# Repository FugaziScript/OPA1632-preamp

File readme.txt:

#OPA1632 preamp

przedwzmacniacz z 2 kanałami, sterowanymi przez przekaźniki. Na wyjściu jest sygnał symetryczny (potrzebny do wysterowania TPA3255). 
Na wejściu akceptowane są sygnały symetryczne, jaki i niesymetryczne. OPA1632 jest w stanie  symetryzować sygnał single-ended, jeżeli jedno z wejść jest dołączone do masy. Zasilanie układów jest z pojedyńczego +12V. Poprzez przetwornicę generującą napięcie ujemne oraz stabilizatory gwarantujące niskie szumy, nie ma potrzeby stosować kondensatorów na wyjściu OPA1632. Wzmocnienie układu wynosi 1. 
Płytka pcb jest bardzo ciasno upakowana, gdyż w obudowie nie było dużo miejsca (jest to największe pcb jakie się zmieściło). Wykonane w technologii tht ze względów na koszty oraz brak precyzji przy wytrawianiu płytki oraz lutowaniu elementów smd.

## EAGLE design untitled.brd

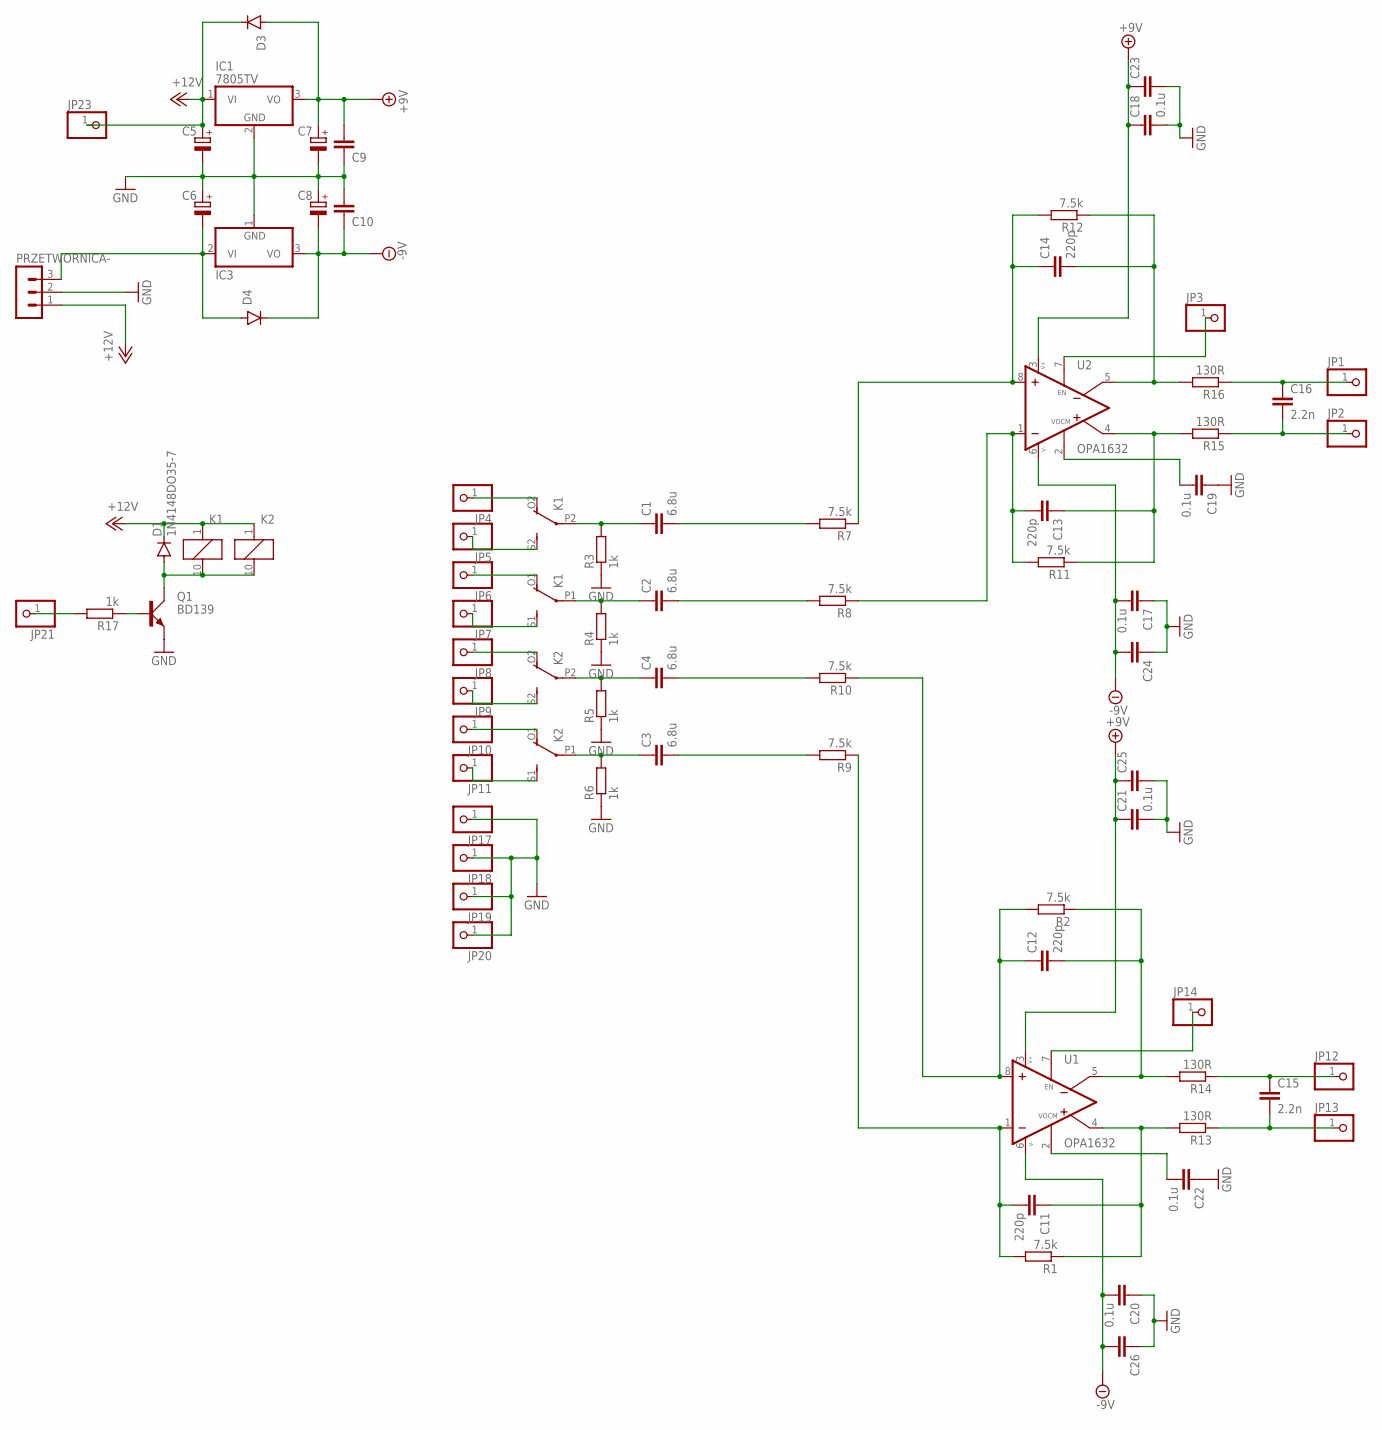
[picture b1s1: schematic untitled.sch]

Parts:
C1, C2, C3, C4: 6.8u; C5B7.2
C5, C6, C7, C8: CPOL-EUE3.5-8; E3,5-8
C9, C10, C23, C24, C25, C26: C-EU050-024X044; C050-024X044
C11, C12, C13, C14: 220p; C075-032X103
C15, C16: 2.2n; C025-024X044
C17, C18, C19, C20, C21, C22: 0.1u; C025-024X044
D1, D3, D4: 1N4148DO35-7; DO35-7
IC1: 7805TV; TO220V
IC3: 79; TO220V
JP1, JP2, JP3, JP4, JP5, JP6, JP7, JP8, JP9, JP10, JP11, JP12, JP13, JP14, JP17, JP18, JP19, JP20, JP21, JP23: PINHD-1X1; 1X01
K1, K2: G6H2-100
PRZETWORNICA-: MA03-1
Q1: BD139; TO126AV
R1, R2, R11, R12: 7.5k; 0204/7
R3, R4, R5, R6, R17: 1k; 0204/7
R7, R8, R9, R10: 7.5k; 0204/5
R13, R14, R15, R16: 130R; 0204/5
U1, U2: OPA1632; PRZEJSCIOWKA

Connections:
+9V: C7.+, C9.2, C18.1, C21.1, C23.1, C25.1, D3.A, IC1.3 (VO), U1.3 (V+), U2.3 (V+)
+12V: C5.+, D1.C, D3.C, IC1.1 (VI), JP23.1, K1.1, K2.1, PRZETWORNICA-.1
-9V: C8.-, C10.1, C17.2, C20.2, C24.2, C26.2, D4.C, IC3.3 (VO), U1.6 (V-), U2.6 (V-)
GND: C5.-, C6.+, C7.-, C8.+, C9.1, C10.2, C17.1, C18.2, C19.1, C20.1, C21.2, C22.1, C23.2, C24.1, C25.2, C26.1, IC1.2 (GND), IC3.1 (GND), JP17.1, JP18.1, JP19.1, JP20.1, PRZETWORNICA-.2, Q1.E, R3.1, R4.1, R5.1, R6.1
unnamed: JP4.1, K1.O2 (O)
unnamed: JP5.1, K1.S2 (S)
unnamed: JP6.1, K1.O1 (O)
unnamed: JP7.1, K1.S1 (S)
unnamed: D1.A, K1.10 (2), K2.10 (2), Q1.C
unnamed: JP10.1, K2.O1 (O)
unnamed: C12.1, R2.2, R10.1, U1.8 (+IN)
unnamed: Q1.B, R17.1
unnamed: JP9.1, K2.S2 (S)
unnamed: JP11.1, K2.S1 (S)
unnamed: JP8.1, K2.O2 (O)
unnamed: C3.2, R9.2
unnamed: C3.1, K2.P1, R6.2
unnamed: C4.1, K2.P2, R5.2
unnamed: C2.1, K1.P1, R4.2
unnamed: C1.1, K1.P2, R3.2
unnamed: C1.2, R7.2
unnamed: C2.2, R8.2
unnamed: C4.2, R10.2
unnamed: JP21.1, R17.2
unnamed: C14.1, R7.1, R12.2, U2.8 (+IN)
unnamed: C13.2, R8.1, R11.2, U2.1 (-IN)
unnamed: C11.2, R1.2, R9.1, U1.1 (-IN)
unnamed: C13.1, R11.1, R15.2, U2.4 (+OUT)
unnamed: C6.-, D4.A, IC3.2 (VI), PRZETWORNICA-.3
unnamed: C14.2, R12.1, R16.2, U2.5 (-OUT)
unnamed: C16.1, JP1.1, R16.1
unnamed: C16.2, JP2.1, R15.1
unnamed: C11.1, R1.1, R13.2, U1.4 (+OUT)
unnamed: C12.2, R2.1, R14.2, U1.5 (-OUT)
unnamed: C19.2, U2.2 (VOCM)
unnamed: JP3.1, U2.7 (EN)
unnamed: C15.1, JP12.1, R14.1
unnamed: C15.2, JP13.1, R13.1
unnamed: C22.2, U1.2 (VOCM)
unnamed: JP14.1, U1.7 (EN)

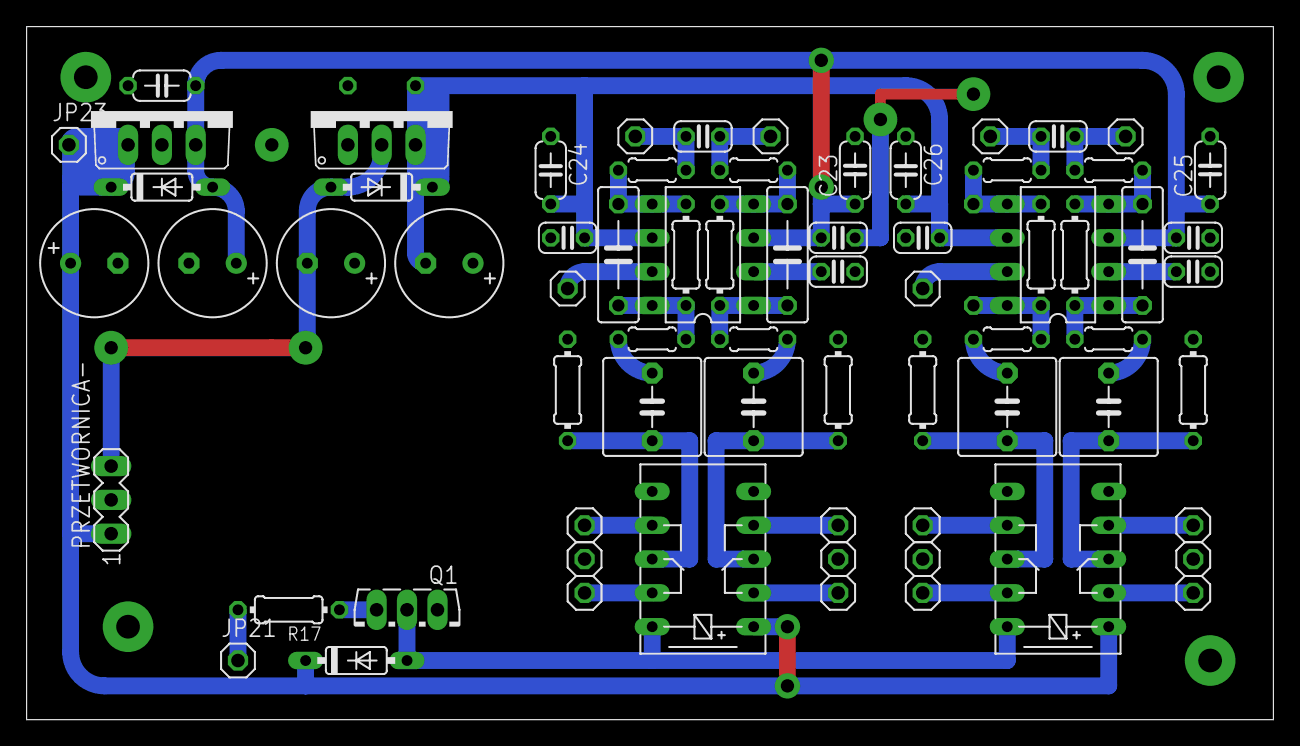
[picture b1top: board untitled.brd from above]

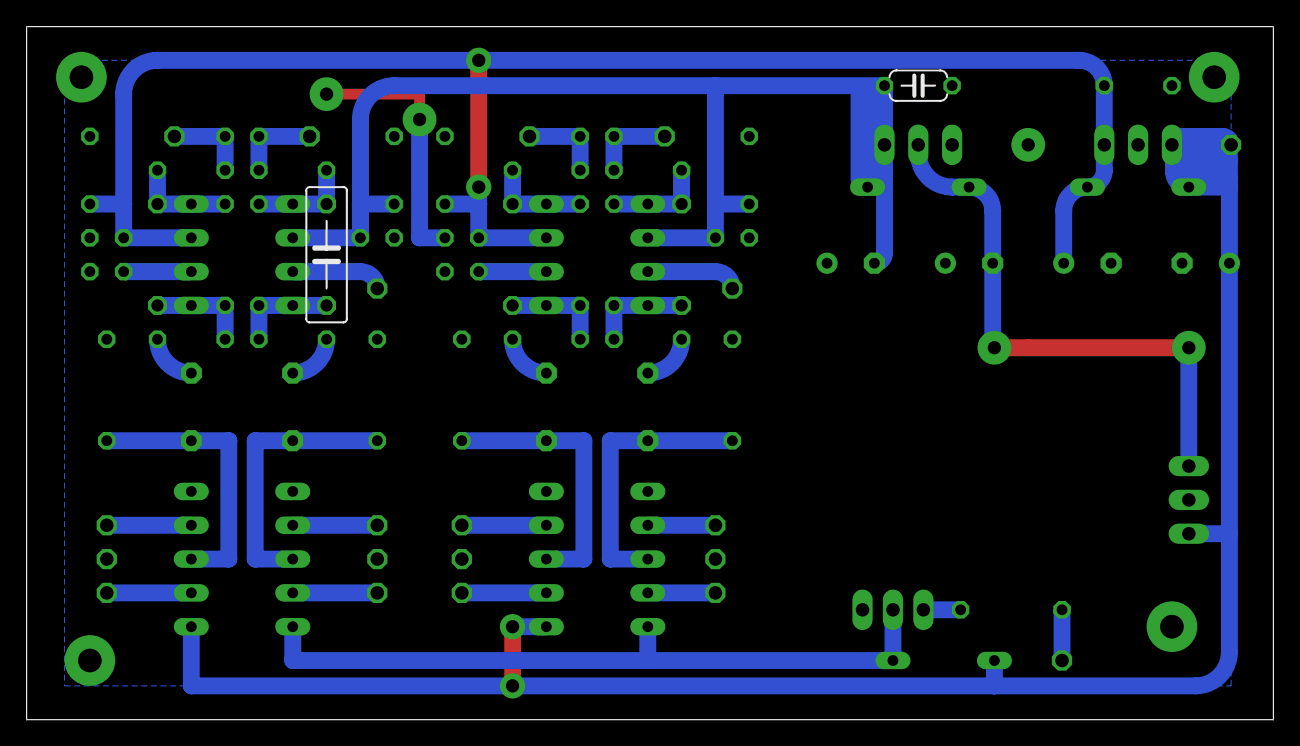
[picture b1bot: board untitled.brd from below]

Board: 2 copper layers, 93.6 x 52.1 mm, 74 parts (2 on the bottom side), 40 nets.

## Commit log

2022-06-29 Delete pcb.jpg
    it will be header
2022-06-29 Rename readme.txt to readme.md
